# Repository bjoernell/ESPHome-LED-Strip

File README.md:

# ESPHome-LED-Strip
This is the repository for my Home Assistant RGB LED-Strip Controller based on ESPHome. 

## Parts list:
I used the following parts to build it:
- Node MCU (ESP8266)
  - control unit with wifi for home assistant
- BD437 Transistor
- Resistors that have a value of approximately 1800Ω
- 8 port dip switch
  - for interrupting the connection between led's and MCU, otherwise the MCU won't boot after disconnecting it from the power supply. I didn't find three pins that are not used       for starting ESPHome or the MCU itself....
- 9V 2A Power Supply
  - the maximum voltage you can use depends on your board, I can power mine with up to 10V so 9V works just fine
- Standard switch
  - to turn the whole circuit on and off in case something is not working (didn't happen so far)
- 6.35mm jack socket and plug 

## Circuit:
The following picture shows a schematic of how i've wired everything up:

I used three transistors one for each color to regulate every pwm value by itself. For the base resistor I calculated a value of 1850Ω. I think it isn't important. I also use a casual switch and an dip switch. The casual switch is just to turn everything on and off if a restart is required. If I want to restart my MCU I have to disconnect the transistors from the MCU and therefore I use a dip switch. My power supply produces about 9V wich is ok for me. It also makes the circuit more simple because I dont have to use a voltage regulator and connect it directly to the MCU's Vin pin. To get the power in my case I used 6.35mm jack socket and plug because I had this laying around.
At the moment the only working KiCad directory at the moment is "Circuit Board" but I will finish the others as soon as my ordered ESP12F modules arive to make the project much smaller.

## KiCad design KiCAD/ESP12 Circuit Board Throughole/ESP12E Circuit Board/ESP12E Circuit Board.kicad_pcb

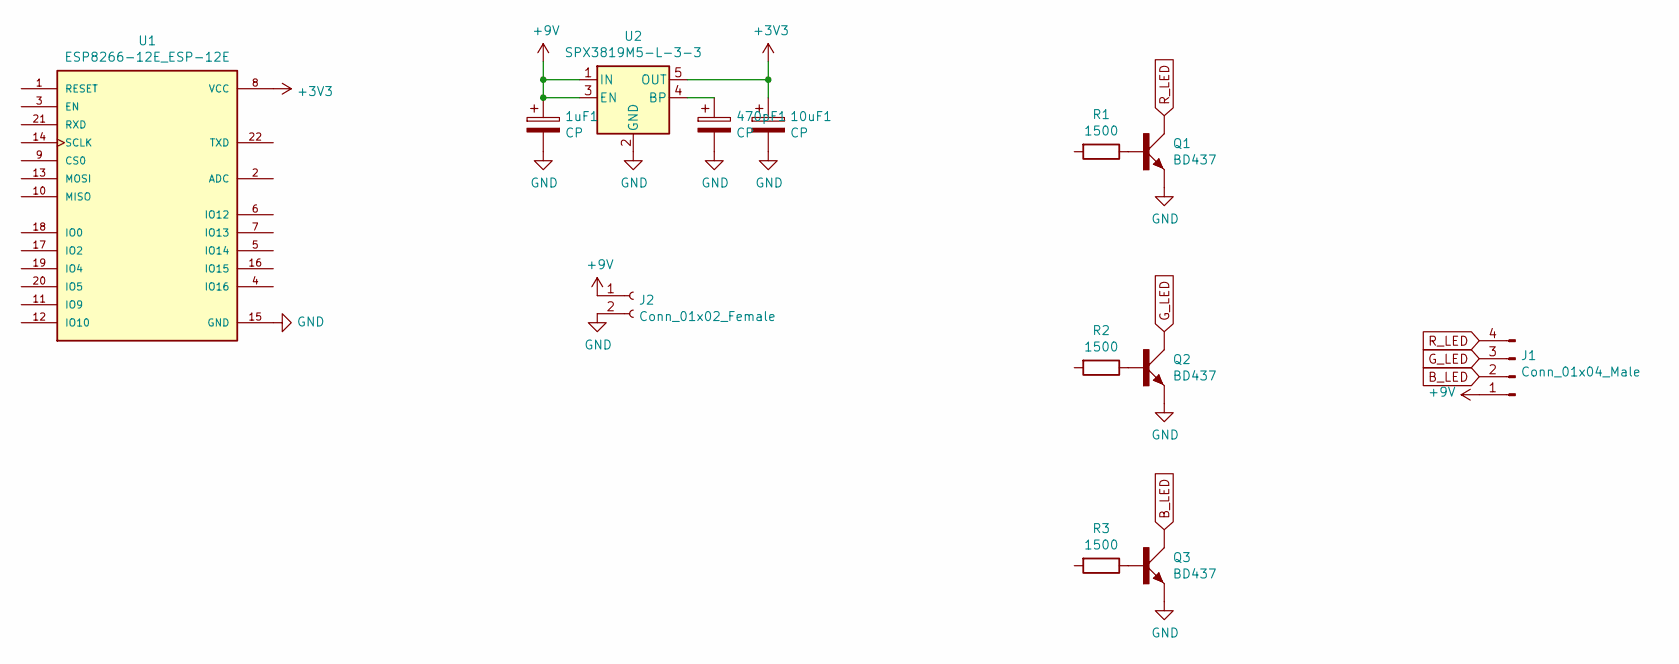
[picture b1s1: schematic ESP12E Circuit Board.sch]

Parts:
1uF1, 10uF1, 470pF1: CP; C_0603_HandSoldering
J1: Conn_01x04_Male; Pin_Header_Straight_1x04_Pitch2.54mm
J2: Conn_01x02_Female; Pin_Header_Straight_1x02_Pitch2.54mm
Q1, Q2, Q3: BD437; TO126AV
R1, R2, R3: 1500; R_Axial_DIN0204_L3.6mm_D1.6mm_P7.62mm_Horizontal
U1: ESP8266-12E_ESP-12E; ESP-12E
U2: SPX3819M5-L-3-3; SOT-23-5_HandSoldering

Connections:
+3V3: 10uF1.1, U1.8 (VCC), U2.5 (OUT)
+9V: 1uF1.1, J1.1, J2.1, U2.1 (IN), U2.3 (EN)
B_LED: J1.2, Q3.C
GND: 1uF1.2, 10uF1.2, 470pF1.2, J2.2, Q1.E, Q2.E, Q3.E, U1.15 (GND), U2.2 (GND)
G_LED: J1.3, Q2.C
unnamed: 470pF1.1, U2.4 (BP)
unnamed: Q1.B, R1.1
unnamed: Q2.B, R2.1
unnamed: Q3.B, R3.1
R_LED: J1.4, Q1.C

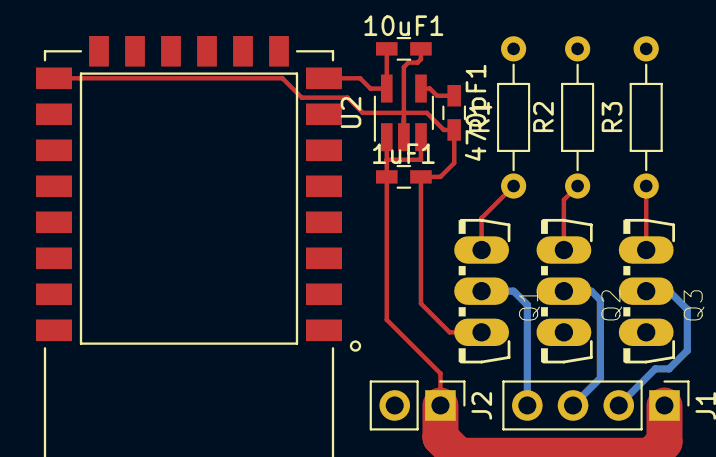
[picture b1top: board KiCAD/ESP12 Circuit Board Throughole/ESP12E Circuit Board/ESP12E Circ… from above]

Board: 2 copper layers, 13 parts (0 on the bottom side), 10 nets.

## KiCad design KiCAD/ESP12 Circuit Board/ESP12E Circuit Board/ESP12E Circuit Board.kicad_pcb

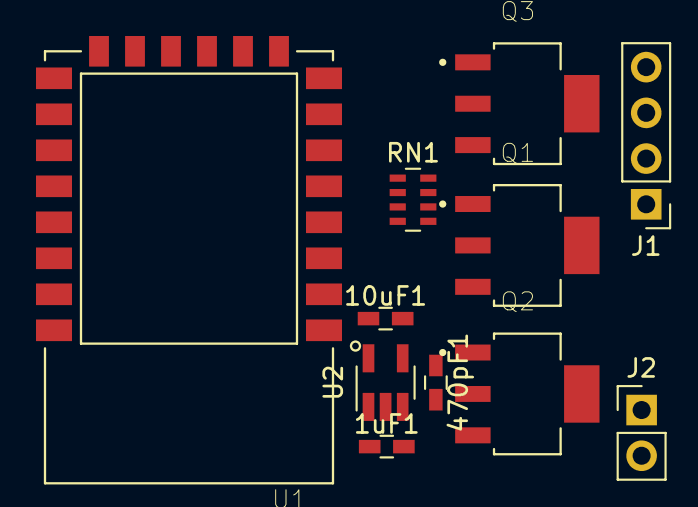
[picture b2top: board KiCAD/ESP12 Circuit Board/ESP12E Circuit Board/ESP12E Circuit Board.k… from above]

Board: 2 copper layers, 11 parts (0 on the bottom side), 10 nets, no tracks yet.

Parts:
1uF1, 10uF1, 470pF1: CP; C_0603_HandSoldering
J1: Conn_01x04_Male; Pin_Header_Straight_1x04_Pitch2.54mm
J2: Conn_01x02_Female; Pin_Header_Straight_1x02_Pitch2.54mm
Q1, Q2, Q3: BCP56; SOT230P700X180-4N
RN1: 1500; R_Array_Concave_4x0603
U1: ESP8266-12E_ESP-12E; ESP-12E
U2: SPX3819M5-L-3-3; SOT-23-5_HandSoldering

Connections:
+3V3: 10uF1.1, U1.8, U2.5
+9V: 1uF1.1, J1.1, J2.1, U2.1, U2.3
B_LED: J1.2, Q3.2
GND: 1uF1.2, 10uF1.2, 470pF1.2, J2.2, Q1.3, Q2.3, Q3.3, U1.15, U2.2
G_LED: J1.3, Q2.2, Q2.4
unnamed: 470pF1.1, U2.4
unnamed: Q1.1, RN1.6
unnamed: Q2.1, RN1.5
unnamed: Q3.1, RN1.4
R_LED: J1.4, Q1.2

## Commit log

2020-11-19 Designed circuit. Should work
2020-11-20 added image for readme.md
2020-11-21 added fusion stl and esphome paths
2020-11-21 added stl files and fusion file
2020-12-06 hothing of interest
2020-12-06 started to design a smaller pcb for ESP12E(hope E will be delivered...)
2020-12-07 worked on the smd circuit
2020-12-10 added throughole circuit board for esp12
2020-12-10 worked on tht circuit
2020-12-10 worked on tht
2020-12-26 added esphome code file
2021-02-03 new schematic. old was wrong
